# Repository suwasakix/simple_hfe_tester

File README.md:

# Simple hFE Tester

トランジスタ hFE 簡易測定器

&nbsp;

## 目次 - Contents

 - [このプリント基板について](#このプリント基板について---about-this-pcb)
 - [ガーバーデータのダウンロード](#ガーバーデータのダウンロード---download-gerber-data)
 - [部品リスト](#部品リスト---parts-list)
 - [便利なアイテム](#便利なアイテム---useful-items)
 - [使用例](#使用例---example-of-use)
 - [回路図](#回路図---pcb-schematic)
 - [レイアウト](#レイアウト---pcb-layout)
 - [開発環境](#開発環境---development-environment)
 - [ライセンスについて](#ライセンスについて---license)

&nbsp;

## このプリント基板について - About this PCB

このプリント基板は、ぺるけさんの [hFEテスター](http://www.op316.com/tubes/mi-audio/hfe-tester.htm) のページで紹介されている簡単版 hFE テスターの回路を実装したものです。  

この基板はトランジスタの直流電流増幅率 (hFE) の簡易測定を目的としたものであり、自作のアンプに使用する半導体部品を選別するのに向いています。選別した半導体部品を第三者に頒布することを目的とする場合は、電流と電圧の両方を調整できるような高機能な測定器が必要になると思います。  

&nbsp;

## ガーバーデータのダウンロード - Download gerber data

こちらのページから「simple_hfe_tester-gerber.zip」のファイルをダウンロードしてください。  

&emsp; https://www.github.com/suwasakix/simple_hfe_tester/releases

このプロジェクトは、各自がプリント基板のガーバーデータをダウンロードして PCB 基板メーカーに基板製造を発注することを前提にしています。個人で発注可能な PCB 基板メーカーは国内外問わずありますが、近年では 10cm 四方以下の基板サイズであれば海外メーカーで格安に製造委託することが可能になりました。発注例として、深圳の Seeed studio が提供する PCB 製造サービス「[Fusion PCB](https://www.fusionpcb.jp)」に基板製造を発注する方法を[こちらのページ](docs/ORDER_PCB.md)で紹介しておきます。

&nbsp;

## 回路図 - PCB schematic

回路の説明は hFE テスターのページに書かれている通りで、測定するトランジスタに 10μA のベース電流が流れるとき 100Ωの両端にかかる電圧から hFE の値を測定します。例えば hFE が 100 のトランジスタの場合、コレクタ電流は 10μA × 100 = 1000μA = 1mA になるので、100Ω にかかる電圧は 1mA × 100Ω = 100mV になります。つまり、テスターで測定した mV の値がそのまま hFE の値になります。

R1 は電流値を測定するための抵抗なので高精度品か、あるいは抵抗値を実測してなるべく 100Ω に近いものを使用してください。

C2 の 0.47uF には積層セラミックコンデンサを使用してください。アルミ電解コンデンサは使用できません。

電源には 5V の AC アダプターか、USB-DC 電源ケーブルを使用してください。DC ジャックは 外径 5.5mm / 内径 2.1mm センタープラスのものが適合します。

&nbsp;

## レイアウト - PCB layout

* 基板サイズ : W 80mm × H 80mm

## 部品リスト - Parts list

* 通販による部品販売では、10個単位などでまとめ売りされている場合がしばしばあります。注文の際にはご注意ください。
* ★ は省略可。
* ☆ は使用しなければ省略可。

|部品種別			|記号					|部品名															|値				|個数		|入手ルート																												|
|:----:				|:----:					|:----:															|:----:			|:----:		|:----:																													|
|抵抗				|R1						|金属皮膜抵抗 1/4W												|100Ω			|1			|[高精度 金属皮膜抵抗 1/2W100Ω ±0.1%][AK_108509_R100]<br>[高精度 金属皮膜抵抗 1/4W100Ω ±0.1%][AK_108504_R100]		|
|					|R2, R3					|金属皮膜抵抗 1/4W												|220kΩ			|2			|[小型 金属皮膜抵抗 1/2WS 220kΩ 1袋100本入][AK_116658_R220k]															|
|コンデンサ			|C1						|電解コンデンサ<br>(直径 6.3mm,<br>リードピッチ 2.5mm)			|100μF			|1			|[100μF35V105℃ ルビコンZLH][AK_102724_C35v100u]																		|
|					|C2						|積層セラミックコンデンサ<br>(リードピッチ 5.0mm)				|0.47μF		|1			|[積層セラミックコンデンサー 0.47μF50V X7R 5mm][AK_108148_C50v0.47u]													|
|スイッチ			|SW1 ★					|トグルスイッチ<br>(3P 1回路2接点 ON-ON)						|-				|1			|[2MS1-T1-B4-M2-Q-E][AK_102399_SW_2MS1-T1-B4-M2-Q-E]<br>[2MS1-T1-B4-VS2-Q-E-S][AK_100300_SW_2MS1-T1-B4-VS2-Q-E-S]		|
|					|SW2					|トグルスイッチ<br>(6P 2回路2接点 ON-ON)						|-				|1			|[2MD1-T1-B4-VS2-Q-E][AK_104028_SW_2MD1-T1-B4-VS2-Q-E]<br>[2MD1-T2-B4-M2-Q-N][AK_100301_SW_2MD1-T2-B4-M2-Q-N]			|
|チェック端子		|TP1 ～ TP7 ☆			|チェック端子													|-				|7			|[チェック端子][AK_C_CCHECKTER]																							|
|ソケット			|J1						|基板型DCジャック<br>(内径2.1mm, 外径5.5mm)						|-				|1			|[MJ-179P][AK_100077_MJ-179P]<br>[2DC0005D100 1パック4個入][AK_101604_2DC0005D100]										|
|					|J2 ☆					|14ピン<br>ゼロプレッシャーICソケット							|-				|1			|[ゼロプレッシャーICソケット 14P][AK_112073_ULO-ZS431-14P1G]															|
|					|J3, J4 ☆				|8ピン 板バネICソケット											|-				|2			|[2227-08-03 1パック10個入][AK_100017_2227-08-03]																		|
|基板スペーサー		|						|黄銅六角スペーサー<br>M3×10mm									|-				|4			|[FB3-10][AK_107313_FB3-10]																								|
|					|						|M3 ネジ								 						|-				|4			|(ホームセンター等で入手可能)																							|

[AK_108509_R100]:								https://akizukidenshi.com/catalog/g/g108509/
[AK_108504_R100]:								https://akizukidenshi.com/catalog/g/g108504/
[AK_116658_R220k]:								https://akizukidenshi.com/catalog/g/g116658/
[AK_102724_C35v100u]:							https://akizukidenshi.com/catalog/g/g102724/
[AK_108148_C50v0.47u]:							https://akizukidenshi.com/catalog/g/g108148/
[AK_102399_SW_2MS1-T1-B4-M2-Q-E]:				https://akizukidenshi.com/catalog/g/g102399/
[AK_100300_SW_2MS1-T1-B4-VS2-Q-E-S]:			https://akizukidenshi.com/catalog/g/g100300/
[AK_104028_SW_2MD1-T1-B4-VS2-Q-E]:				https://akizukidenshi.com/catalog/g/g104028/
[AK_100301_SW_2MD1-T2-B4-M2-Q-N]:				https://akizukidenshi.com/catalog/g/g100301/
[AK_C_CCHECKTER]:								https://akizukidenshi.com/catalog/c/ccheckter/
[AK_100077_MJ-179P]:							https://akizukidenshi.com/catalog/g/g100077/
[AK_101604_2DC0005D100]:						https://akizukidenshi.com/catalog/g/g101604/
[AK_112073_ULO-ZS431-14P1G]:					https://akizukidenshi.com/catalog/g/g112073/
[AK_100017_2227-08-03]:							https://akizukidenshi.com/catalog/g/g100017/
[AK_107313_FB3-10]:								https://akizukidenshi.com/catalog/g/g107313/

R1 は金属皮膜抵抗の高精度品を使用するか、あるいは誤差±1%の金属皮膜抵抗から選別したものを割り当てます。普及価格帯のデジタルマルチメーターの場合、抵抗値の確度（測定誤差）はおおよそ ±0.5% ～ ±1.0% といったところなので、高精度品を使用した方が外れは少ないことになります。ただし、高精度品を使用する場合でも部品の不良チェックのために抵抗値は実測しておくようにしてください。

SW1 は電源スイッチですが、省略することもできます。省略する場合は JP1 のパターンをショートしてください。

J2 は中大型トランジスタ、J3, J4 は小型トランジスタ用のソケットです。使わないソケットは省略することもできます。TP5 ～ TP7 から線出しして IC クリップで測定するトランジスタを繋いでもよいです。

&nbsp;

## 便利なアイテム - Useful items

|部品名																			|入手ルート																							|
|:----:																			|:----:																								|
|ACアダプター 5V<br>(DCプラグ内径2.1mm, 外径5.5mm,<br>センタープラス)			|[AD-T50P200][AK_111996_ACDC5V_AD-T50P200]<br>[M050200-A010JP][AK_111996_ACDC5V_M050200-A010JP]		|
|USB-DC電源ケーブル<br>(DCプラグ内径2.1mm, 外径5.5mm,<br>センタープラス)		|[DC-5521A][SG_5AK2-DTDU_DCP_DC-5521A]																|
|テストリード<br>(バナナプラグ ⇔ ICクリップ)									|[TLA-106][AK_112359_TLA-106]																		|
|テストリード<br>(ICクリップ両端)												|[TLA-105][AK_112419_TLA-105]<br>[TLA-101][AK_111765_TLA-101]										|

[AK_111996_ACDC5V_AD-T50P200]:					https://akizukidenshi.com/catalog/g/g111996/
[AK_111996_ACDC5V_M050200-A010JP]:				https://akizukidenshi.com/catalog/g/g118205/
[SG_5AK2-DTDU_DCP_DC-5521A]:					https://www.sengoku.co.jp/mod/sgk_cart/detail.php?code=5AK2-DTDU
[AK_112359_TLA-106]:							https://akizukidenshi.com/catalog/g/g112359/
[AK_112419_TLA-105]:							https://akizukidenshi.com/catalog/g/g112419/
[AK_111765_TLA-101]:							https://akizukidenshi.com/catalog/g/g111765/

&nbsp;

## 使用例 - Example of use

型番が 2SC または 2SD で始まるトランジスタ（NPN 型トランジスタ）の場合は、SW2 を下側に合わせて測定します。写真は 2SC1815(GR) を測定した場合で、hFE の値は電圧 (mV) の大きさと同じ 282 になります。

型番が 2SA または 2SB で始まるトランジスタ（PNP 型トランジスタ）の場合は、SW2 を上側に合わせて測定します。写真は 2SA1015(GR) を測定した場合で、hFE の値は電圧 (mV) の大きさと同じ 374 になります。

2SC1815、2SA1015 はいずれも３番ピンがベース端子なので、左側にベース端子がくるようにソケットに差して測定してください。

&nbsp;

## 開発環境 - Development environment

このプリント基板の設計データは、[KiCad](https://www.kicad.org) 9.0 で作成しています。基板のデータは KiCad 9.0 以降で編集することができます。  

なお、この基板のデータを改変するには KiCad ライブラリ [Victwale](https://github.com/suwasakix/Victwale) を必要とします。  

&nbsp;

## ライセンスについて - License

このプリント基板の設計データのライセンスは [Creative Commons CC-BY 4.0 License](https://creativecommons.org/licenses/by/4.0/legalcode) です。

- 上記設計データの著作権は作者 (suwasakix) が保持します。ただし、著作権が生じるのは設計データのレイアウトのみであり、回路図に著作権は生じません。

- 上記設計データは、何の制限もなく私的に利用することができます。データを自由に改変して私的に利用することもできます。

- 上記設計データに変更を加えることなく製造したプリント基板は、商用・非商用を問わず何の制限もなく第三者に頒布することができます。

- 上記設計データの改変物、または改変物をもとに製造したプリント基板（二次創作物）を第三者に頒布するには、原作品が著作権者 (suwasakix) のものであること、および当該作品が二次創作物であることを明示する必要があります。一例としては、原作品の著作権者、および二次創作物の著作権者を当該作品に明示すれば問題ありません。

  - なお、それらを明示する手段は当該作品の実物以外に、当該作品の設計データの一時配布元でもよいものとします（当該作品に著作権者の情報を記載する物理的なスペースがない場合には、一時配布元に著作権者の情報を記載することで代えることが可能です）。その場合、当該作品の実物にデータの一時配布元が記載されていなければなりません。

- 上記設計データの二次創作物には、原作品とは異なるライセンスを適用することができます。

- 上記ライセンスは著作権者からの一方的な利用許諾条件です。利用するにあたり著作権者への連絡は一切不要です。

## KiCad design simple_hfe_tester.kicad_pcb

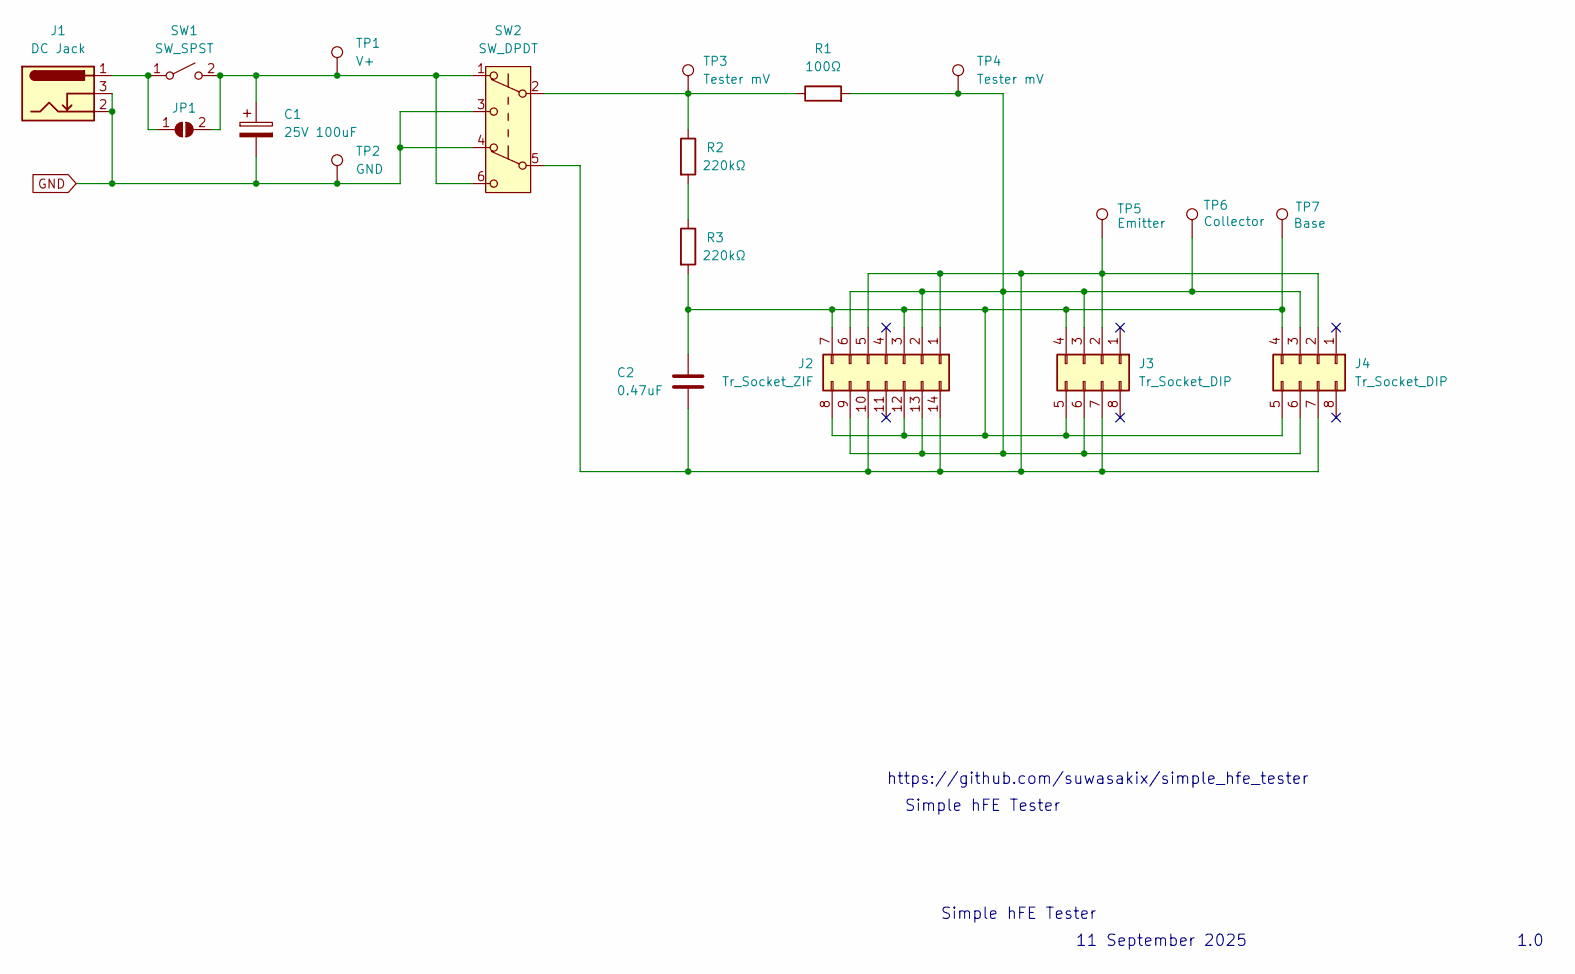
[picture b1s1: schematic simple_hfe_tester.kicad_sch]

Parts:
C1: 25V 100uF; CP_Radial_D6.3mm_P2.50mm
C2: 0.47uF; C_Disc_D5.0mm_W2.5mm_P5.00mm
J1: DC Jack; BarrelJack_Horizontal
J2: Tr_Socket_ZIF; DIP-14_W7.62mm_Socket
J3, J4: Tr_Socket_DIP; DIP-8_W7.62mm_Socket
JP1: SolderJumper-2_P1.3mm_Open_TrianglePad1.0x1.5mm
R1: 100Ω; R_Axial_DIN0411_L9.9mm_D3.6mm_P12.70mm_Horizontal
R2, R3: 220kΩ; R_Axial_DIN0207_L6.3mm_D2.5mm_P7.62mm_Horizontal
SW1: SW_SPST; SW_DPDT_2MS1-T1-B4-VS2-Q-E
SW2: SW_DPDT; SW_DPDT_2MD1-T1-B4-VS2-Q-E
TP1: V+; Pin_D1.0mm_L10.0mm
TP2: GND; Pin_D1.0mm_L10.0mm
TP3, TP4: Tester mV; Pin_D1.0mm_L10.0mm
TP5: Emitter; Pin_D1.0mm_L10.0mm
TP6: Collector; Pin_D1.0mm_L10.0mm
TP7: Base; Pin_D1.0mm_L10.0mm

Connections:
GND: C1.2, J1.2, J1.3, SW2.3 (C), SW2.4 (A), TP2.1
unnamed: C2.2, J2.1, J2.5, J2.10, J2.14, J3.2, J3.7, J4.2, J4.7, SW2.5 (B), TP5.1
unnamed: C2.1, J2.3, J2.7, J2.8, J2.12, J3.4, J3.5, J4.4, J4.5, R3.2, TP7.1
unnamed: J2.2, J2.6, J2.9, J2.13, J3.3, J3.6, J4.3, J4.6, R1.2, TP4.1, TP6.1
unnamed: J1.1, JP1.1 (A), SW1.1 (A)
unnamed: C1.1, JP1.2 (B), SW1.2 (B), SW2.1 (A), SW2.6 (C), TP1.1
unnamed: R1.1, R2.1, SW2.2 (B), TP3.1
unnamed: R2.2, R3.1

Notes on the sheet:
Simple hFE Tester
1.0
11 September 2025
https://github.com/suwasakix/simple_hfe_tester

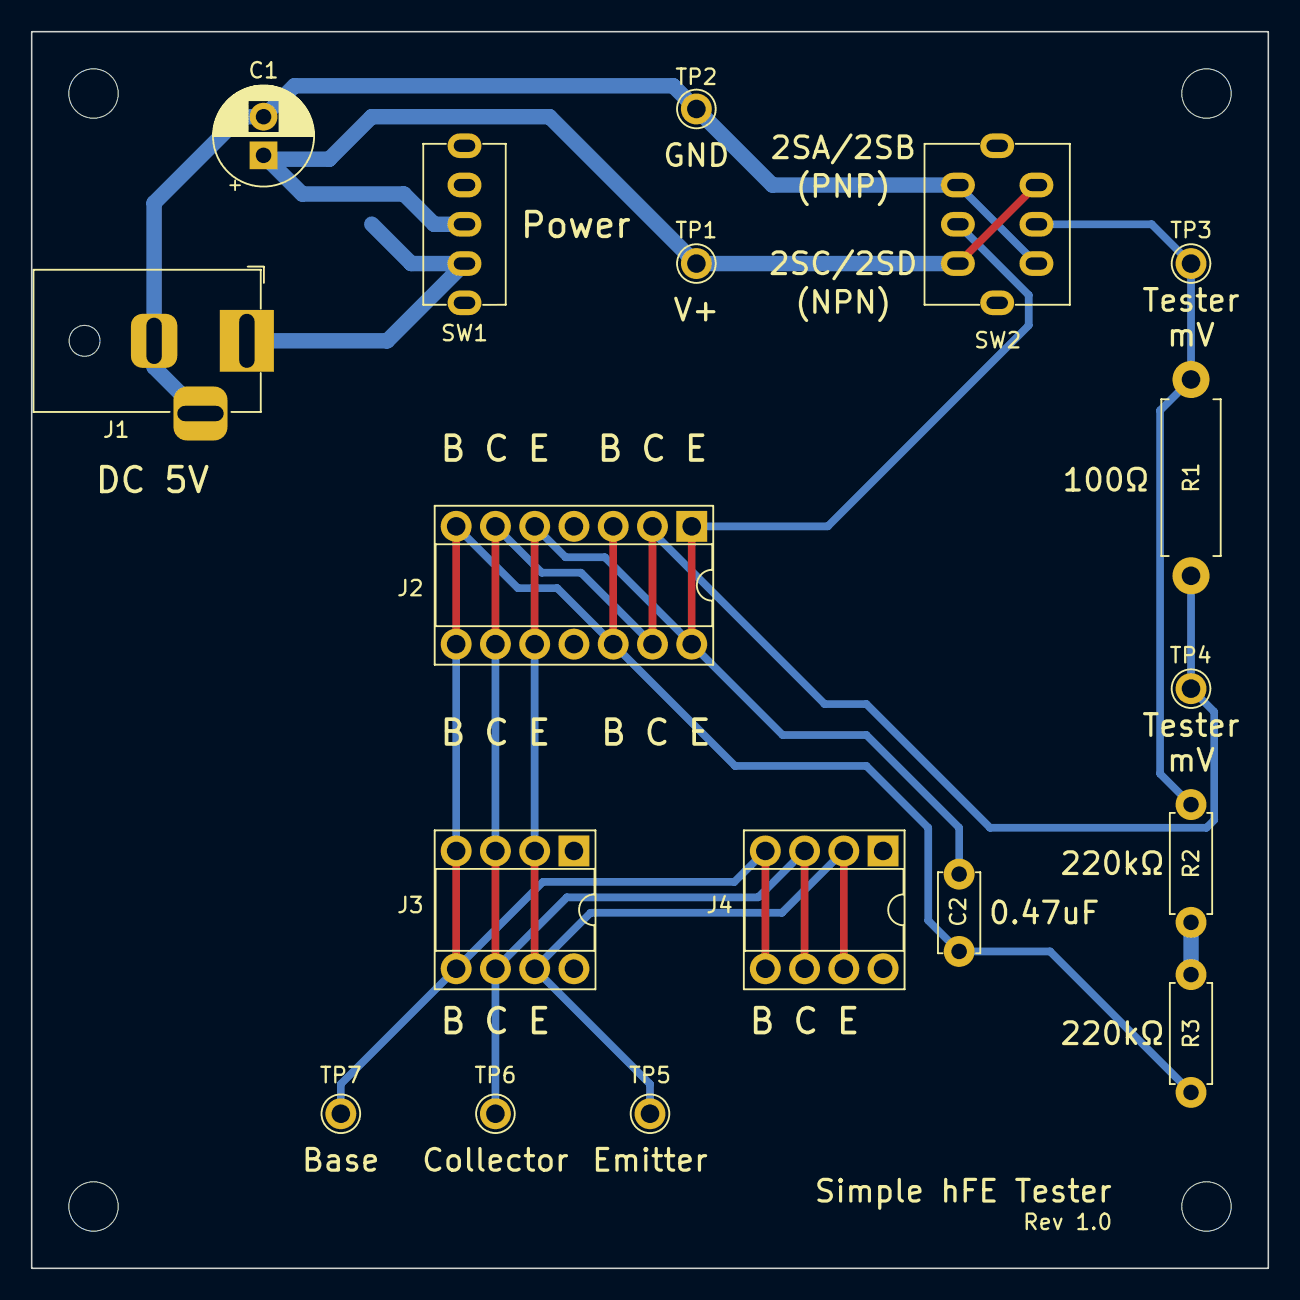
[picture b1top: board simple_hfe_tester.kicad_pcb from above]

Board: 2 copper layers, 80.0 x 80.0 mm, 19 parts (1 on the bottom side), 8 nets.

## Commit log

2025-09-24 First release
    * based on KiCAD 9.0
2025-12-17 Update documents
    * Add LICENSE
    * Update README.md

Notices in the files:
simple_hfe_tester.kicad_pcb:
© suwasakix 2025, licensed under CC-BY-4.0
